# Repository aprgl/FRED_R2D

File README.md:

Little Resolver to Digital board for FRED (ABB IRB 2000).

[Ongoing google doc bring-up notes](https://docs.google.com/document/d/1SvePxEv6x2LG5fbGa1SZI07iUhBEWdyZOOTjJPw_SJs)

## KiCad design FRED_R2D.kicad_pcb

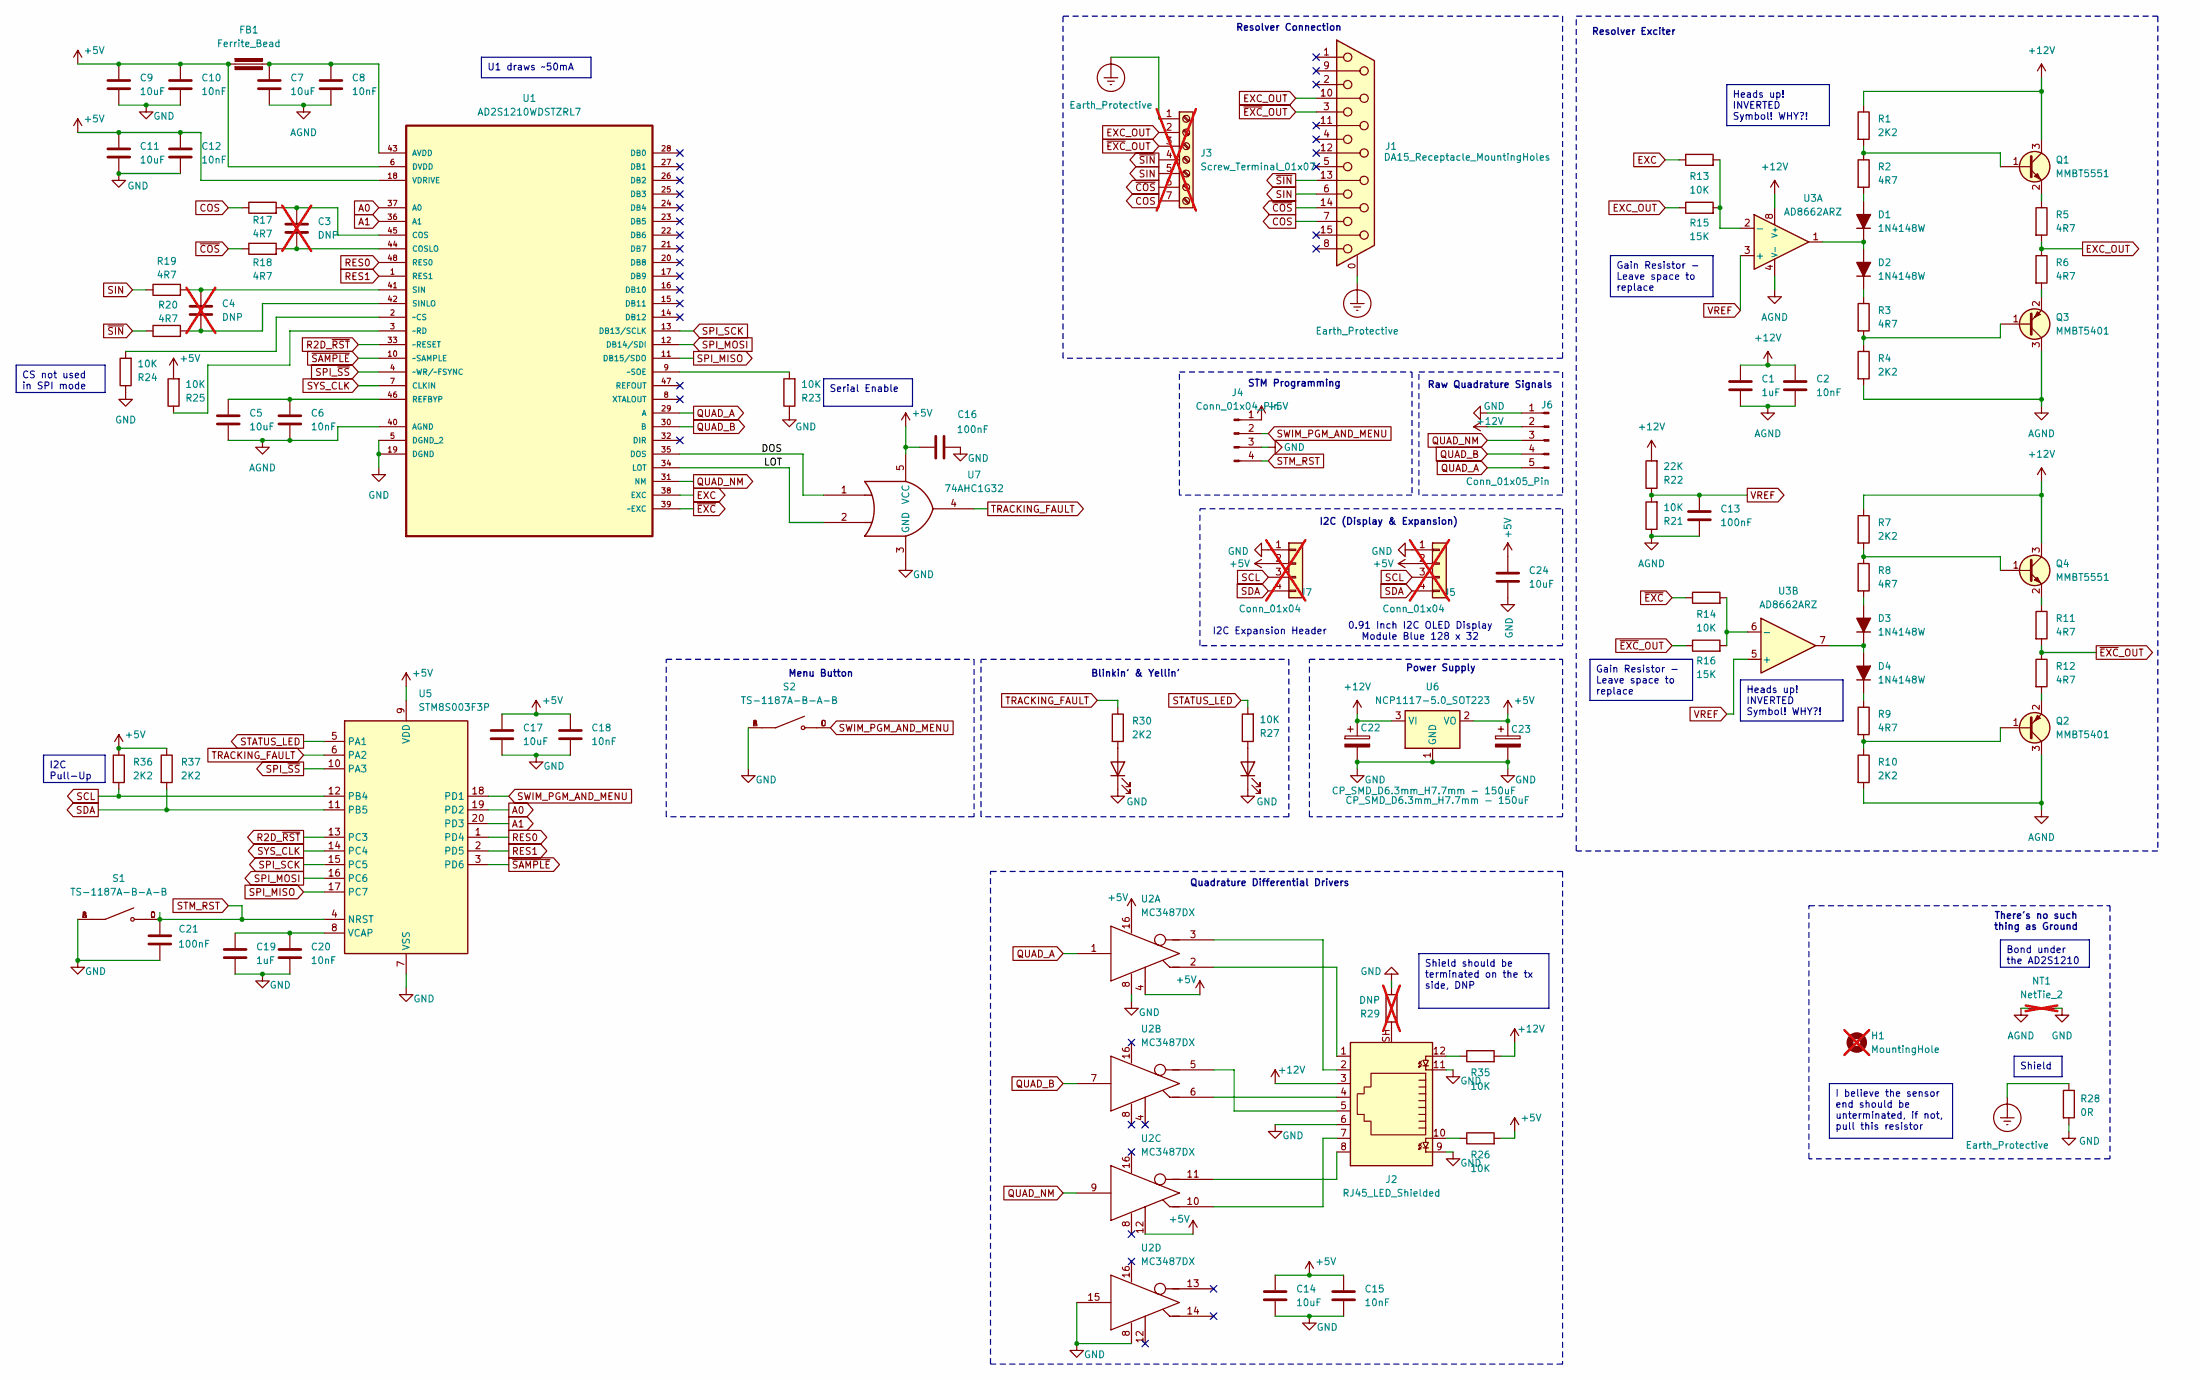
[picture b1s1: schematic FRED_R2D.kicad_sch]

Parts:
C1, C19: 1uF; C_0603_1608Metric; LCSC C15849
C2, C6, C8, C10, C12, C15, C18, C20: 10nF; C_0603_1608Metric; LCSC C57112
C3, C4: DNP; C_0603_1608Metric; not fitted
C5, C7, C9, C11, C14, C17, C24: 10uF; C_0603_1608Metric; LCSC C96446
C13, C16, C21: 100nF; C_0603_1608Metric; LCSC C14663
C22, C23: CP_SMD_D6.3mm_H7.7mm - 150uF; CP_Elec_6.3x7.7; LCSC C249984
D1, D2, D3, D4: 1N4148W; D_SOD-123; LCSC C81598
D5, D6: LED; LED_0603_1608Metric; LCSC C2286
FB1: Ferrite_Bead; Fuse_0603_1608Metric; LCSC C1002
H1: MountingHole; MountingHole_2.2mm_M2; not fitted
J1: DA15_Receptacle_MountingHoles; DSUB-15_Female_Horizontal_P2.77x2.84mm_EdgePinOffset7.70mm_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; LCSC C77836
J2: RJ45_LED_Shielded; RJ45_Amphenol_RJHSE538X; LCSC C464587
J3: Screw_Terminal_01x07; TerminalBlock_Phoenix_MPT-0,5-7-2.54_1x07_P2.54mm_Horizontal; not fitted
J4: Conn_01x04_Pin; Molex_PicoBlade_53047-0410_1x04_P1.25mm_Vertical
J5, J7: Conn_01x04; PinHeader_1x04_P2.54mm_Vertical; not fitted
J6: Conn_01x05_Pin; JST_PH_B5B-PH-K_1x05_P2.00mm_Vertical; LCSC C157993
NT1: NetTie_2; NetTie-2_SMD_Pad0.5mm; not fitted
Q1, Q4: MMBT5551; SOT-23; LCSC C2145
Q2, Q3: MMBT5401; SOT-23; LCSC C8326
R1, R4, R7, R10, R30, R36, R37: 2K2; R_0603_1608Metric; LCSC C4190
R2, R3, R5, R6, R8, R9, R11, R12, R17, R18, R19, R20: 4R7; R_0603_1608Metric; LCSC C23164
R13, R14, R21, R23, R24, R25, R26, R27, R35: 10K; R_0603_1608Metric; LCSC C25804
R15, R16: 15K; R_0603_1608Metric; LCSC C22809
R22: 22K; R_0603_1608Metric; LCSC C31850
R28: 0R; R_0603_1608Metric; LCSC C21189
R29: DNP; R_0603_1608Metric; not fitted
S1, S2: TS-1187A-B-A-B; SW_TS-1187A-B-A-B; PARTREV A0; LCSC C318884
U1: AD2S1210WDSTZRL7; QFP50P900X900X160-48N; MPN AD2S1210WDSTZRL7; LCSC C459871
U2: MC3487DX; SOIC-16_3.9x9.9mm_P1.27mm; LCSC C7309
U3: AD8662ARZ; SO-8_3.9x4.9mm_P1.27mm; LCSC C28133
U5: STM8S003F3P; TSSOP-20_4.4x6.5mm_P0.65mm; LCSC C52717
U6: NCP1117-5.0_SOT223; SOT-223-3_TabPin2; LCSC C185806
U7: 74AHC1G32; SOT-23-5; LCSC C2861488

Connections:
+5V: C9.1, C10.1, C11.1, C12.1, C14.1, C15.1, C16.1, C17.1, C18.1, C23.1, C24.1, FB1.1, J4.1, J5.2, J7.2, R25.2, R26.2, R36.1, R37.1, U1.6 (DVDD), U1.18 (VDRIVE), U2.4 (ENABLE), U2.12 (ENABLE), U2.16 (VCC), U5.9 (VDD), U6.2 (VO), U7.5 (VCC)
+12V: C1.1, C2.1, C22.1, J2.3, J6.2, Q1.3 (C), Q4.3 (C), R1.1, R7.1, R22.2, R35.2, U3.8 (V+), U6.3 (VI)
/DOS: U1.35 (DOS), U7.1
/LOT: U1.34 (LOT), U7.2
A0: U1.37 (A0), U5.19 (PD2)
A1: U1.36 (A1), U5.20 (PD3)
AGND: C1.2, C2.2, C5.2, C6.2, C7.2, C8.2, C13.2, NT1.1, Q2.3 (C), Q3.3 (C), R4.2, R10.2, R21.1, U1.40 (AGND), U3.4 (V-)
COS: J1.7, J3.7, R17.1
EXC: R13.1, U1.38 (EXC)
EXC_OUT: J1.10, J3.2, R5.2, R6.1, R15.1
Earth_Protective: J1.0 (PAD), J3.1, R28.1
GND: C9.2, C10.2, C11.2, C12.2, C14.2, C15.2, C16.2, C17.2, C18.2, C19.2, C20.2, C21.1, C22.2, C23.2, C24.2, D5.1 (K), D6.1 (K), J2.6, J2.9, J2.11, J4.3, J5.1, J6.1, J7.1, NT1.2, R23.1, R24.1, R28.2, R29.2, S1.A, S1.B, S2.A, S2.B, U1.5 (DGND_2), U1.19 (DGND), U2.8 (GND), U2.15 (INPUT), U5.7 (VSS), U6.1 (GND), U7.3 (GND)
unnamed: D1.2 (A), R2.2
unnamed: D1.1 (K), D2.2 (A), U3.1
unnamed: D2.1 (K), R3.1
unnamed: D3.2 (A), R8.2
unnamed: D3.1 (K), D4.2 (A), U3.7
unnamed: D4.1 (K), R9.1
unnamed: D5.2 (A), R27.1
unnamed: D6.2 (A), R30.2
unnamed: J2.10, R26.1
unnamed: J2.12, R35.1
unnamed: J2.SH, R29.1
unnamed: Q1.1 (B), R1.2, R2.1
unnamed: Q1.2 (E), R5.1
unnamed: Q2.1 (B), R9.2, R10.1
unnamed: Q2.2 (E), R12.2
unnamed: Q3.1 (B), R3.2, R4.1
unnamed: Q3.2 (E), R6.2
unnamed: Q4.1 (B), R7.2, R8.1
unnamed: Q4.2 (E), R11.1
unnamed: C7.1, C8.1, FB1.2, U1.43 (AVDD)
unnamed: C3.1, R17.2, U1.45 (COS)
unnamed: C3.2, R18.2, U1.44 (COSLO)
unnamed: C5.1, C6.1, U1.46 (REFBYP)
unnamed: C4.1, R19.2, U1.41 (SIN)
unnamed: C4.2, R20.2, U1.42 (SINLO)
unnamed: R24.2, U1.2 (~CS)
unnamed: R25.1, U1.3 (~RD)
unnamed: R23.2, U1.9 (~SOE)
unnamed: J2.1, U2.2 (OUT+)
unnamed: J2.2, U2.3 (OUT-)
unnamed: J2.4, U2.6 (OUT+)
unnamed: J2.5, U2.5 (OUT-)
unnamed: J2.7, U2.10 (OUT+)
unnamed: J2.8, U2.11 (OUT-)
unnamed: R13.2, R15.2, U3.2 (-)
unnamed: R14.2, R16.2, U3.6 (-)
unnamed: C19.1, C20.1, U5.8 (VCAP)
QUAD_A: J6.5, U1.29 (A), U2.1 (INPUT)
QUAD_B: J6.4, U1.30 (B), U2.7 (INPUT)
QUAD_NM: J6.3, U1.31 (NM), U2.9 (INPUT)
R2D_~RST: U1.33 (~RESET), U5.13 (PC3)
RES0: U1.48 (RES0), U5.1 (PD4)
RES1: U1.1 (RES1), U5.2 (PD5)
SCL: J5.3, J7.3, R36.2, U5.12 (PB4)
SDA: J5.4, J7.4, R37.2, U5.11 (PB5)
SIN: J1.6, J3.5, R19.1
SPI_MISO: U1.11 (DB15/SDO), U5.17 (PC7)
SPI_MOSI: U1.12 (DB14/SDI), U5.16 (PC6)
SPI_SCK: U1.13 (DB13/SCLK), U5.15 (PC5)
SPI_~SS: U1.4 (~WR/~FSYNC), U5.10 (PA3)
STATUS_LED: R27.2, U5.5 (PA1)
STM_RST: C21.2, J4.4, S1.C, S1.D, U5.4 (NRST)
SWIM_PGM_AND_MENU: J4.2, S2.C, S2.D, U5.18 (PD1)
SYS_CLK: U1.7 (CLKIN), U5.14 (PC4)
TRACKING_FAULT: R30.1, U5.6 (PA2), U7.4
VREF: C13.1, R21.2, R22.1, U3.3 (+), U3.5 (+)
~COS: J1.14, J3.6, R18.1
~EXC: R14.1, U1.39 (~EXC)
~EXC_OUT: J1.3, J3.3, R11.2, R12.1, R16.1
~SAMPLE: U1.10 (~SAMPLE), U5.3 (PD6)
~SIN: J1.13, J3.4, R20.1

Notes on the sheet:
I2C Pull-Up
Bond under the AD2S1210
Gain Resistor - Leave space to replace
Heads up! INVERTED Symbol! WHY?!
CS not used in SPI mode
Shield should be terminated on the tx side, DNP
I believe the sensor end should be unterminated, if not, pull this resistor
Shield
U1 draws ~50mA
Serial Enable
I2C Expansion Header
Power Supply
Quadrature Differential Drivers
Blinkin' & Yellin'
STM Programming
Raw Quadrature Signals
Resolver Connection
Resolver Exciter
I2C (Display & Expansion)
There's no such thing as Ground
Menu Button
0.91 Inch I2C OLED Display Module Blue 128 x 32

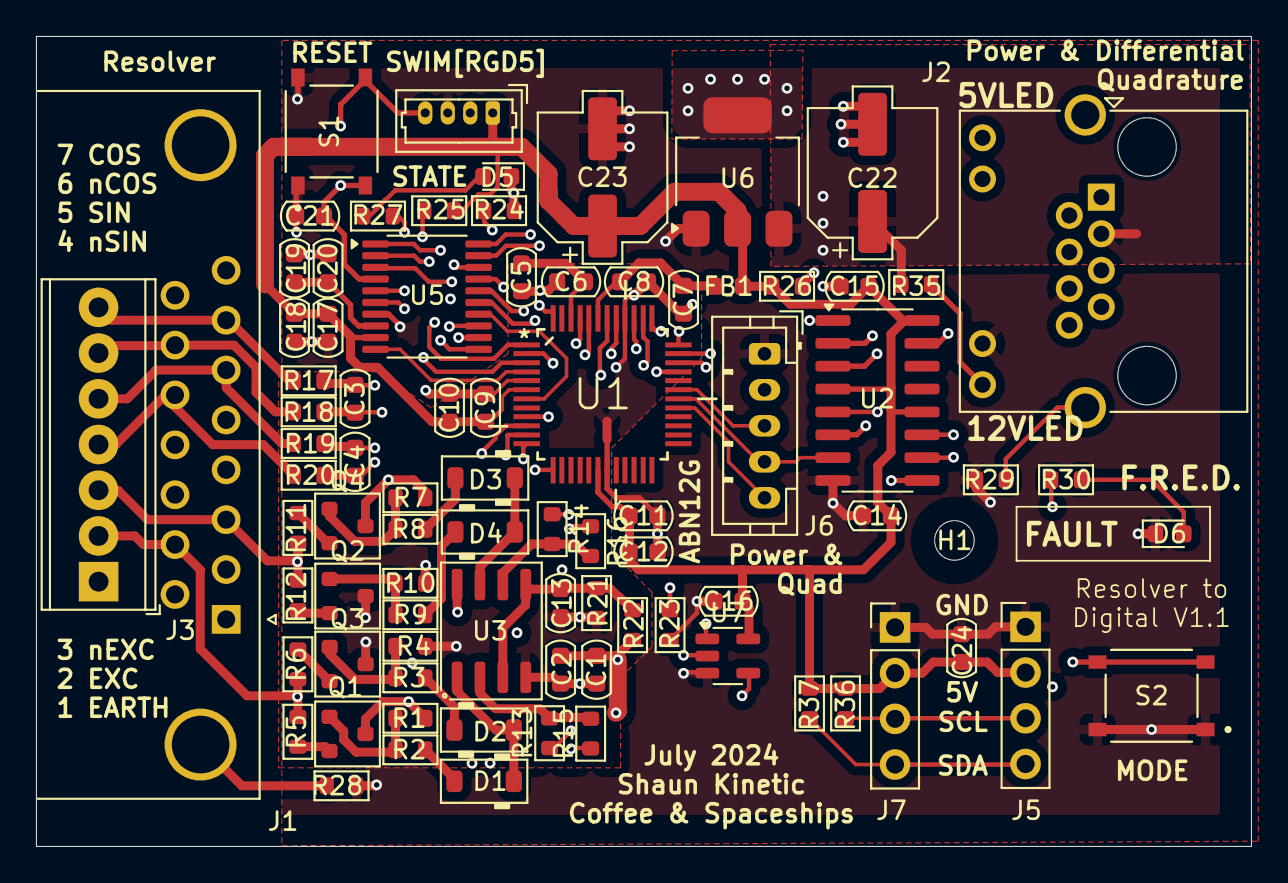
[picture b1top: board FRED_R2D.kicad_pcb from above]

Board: 4 copper layers, 67.5 x 45.0 mm, 85 parts (0 on the bottom side), 73 nets.

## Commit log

2024-06-25 Added git ignore for kicad
2024-06-28 V1.0 Commit
2024-06-28 Fxied name issue, reverted to compiling blinky
2025-07-29 Version 1.1 for mfg
2025-07-29 Create README.md
    Added a readme and link to notes on the bring-up
